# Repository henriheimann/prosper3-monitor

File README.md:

<br/>
<br/>
<br/>

# Prosper III Monitor

This repository contains the source code accompanying my master's thesis "Entwicklung einer digitalen Lösung zur Unterstützung von Tactical Urbanism auf Prosper III" (Development of a Digital Solution to Support Tactical Urbanism on Prosper III) at [Hochschule Ruhr West](https://www.hochschule-ruhr-west.de/). It includes hardware designs and embedded software for LoRaWAN-based sensor nodes to collect microclimate and irrigation data, as well as a web application and infrastructure to manage sensor nodes and view data.

<br/>
<br/>

Climate sensor nodes contain an ambient light sensor, a temperature and humidity sensor, as well as an optional infrared temperature sensor which can be used to measure surface temperatures from afar.

<br/>
<br/>
<br/>

Irrigation sensor nodes use a capacitive soil moisture sensor and the microcontrollers' embedded temperature sensor to monitor raised beds.

<br/>
<br/>

## Frontend

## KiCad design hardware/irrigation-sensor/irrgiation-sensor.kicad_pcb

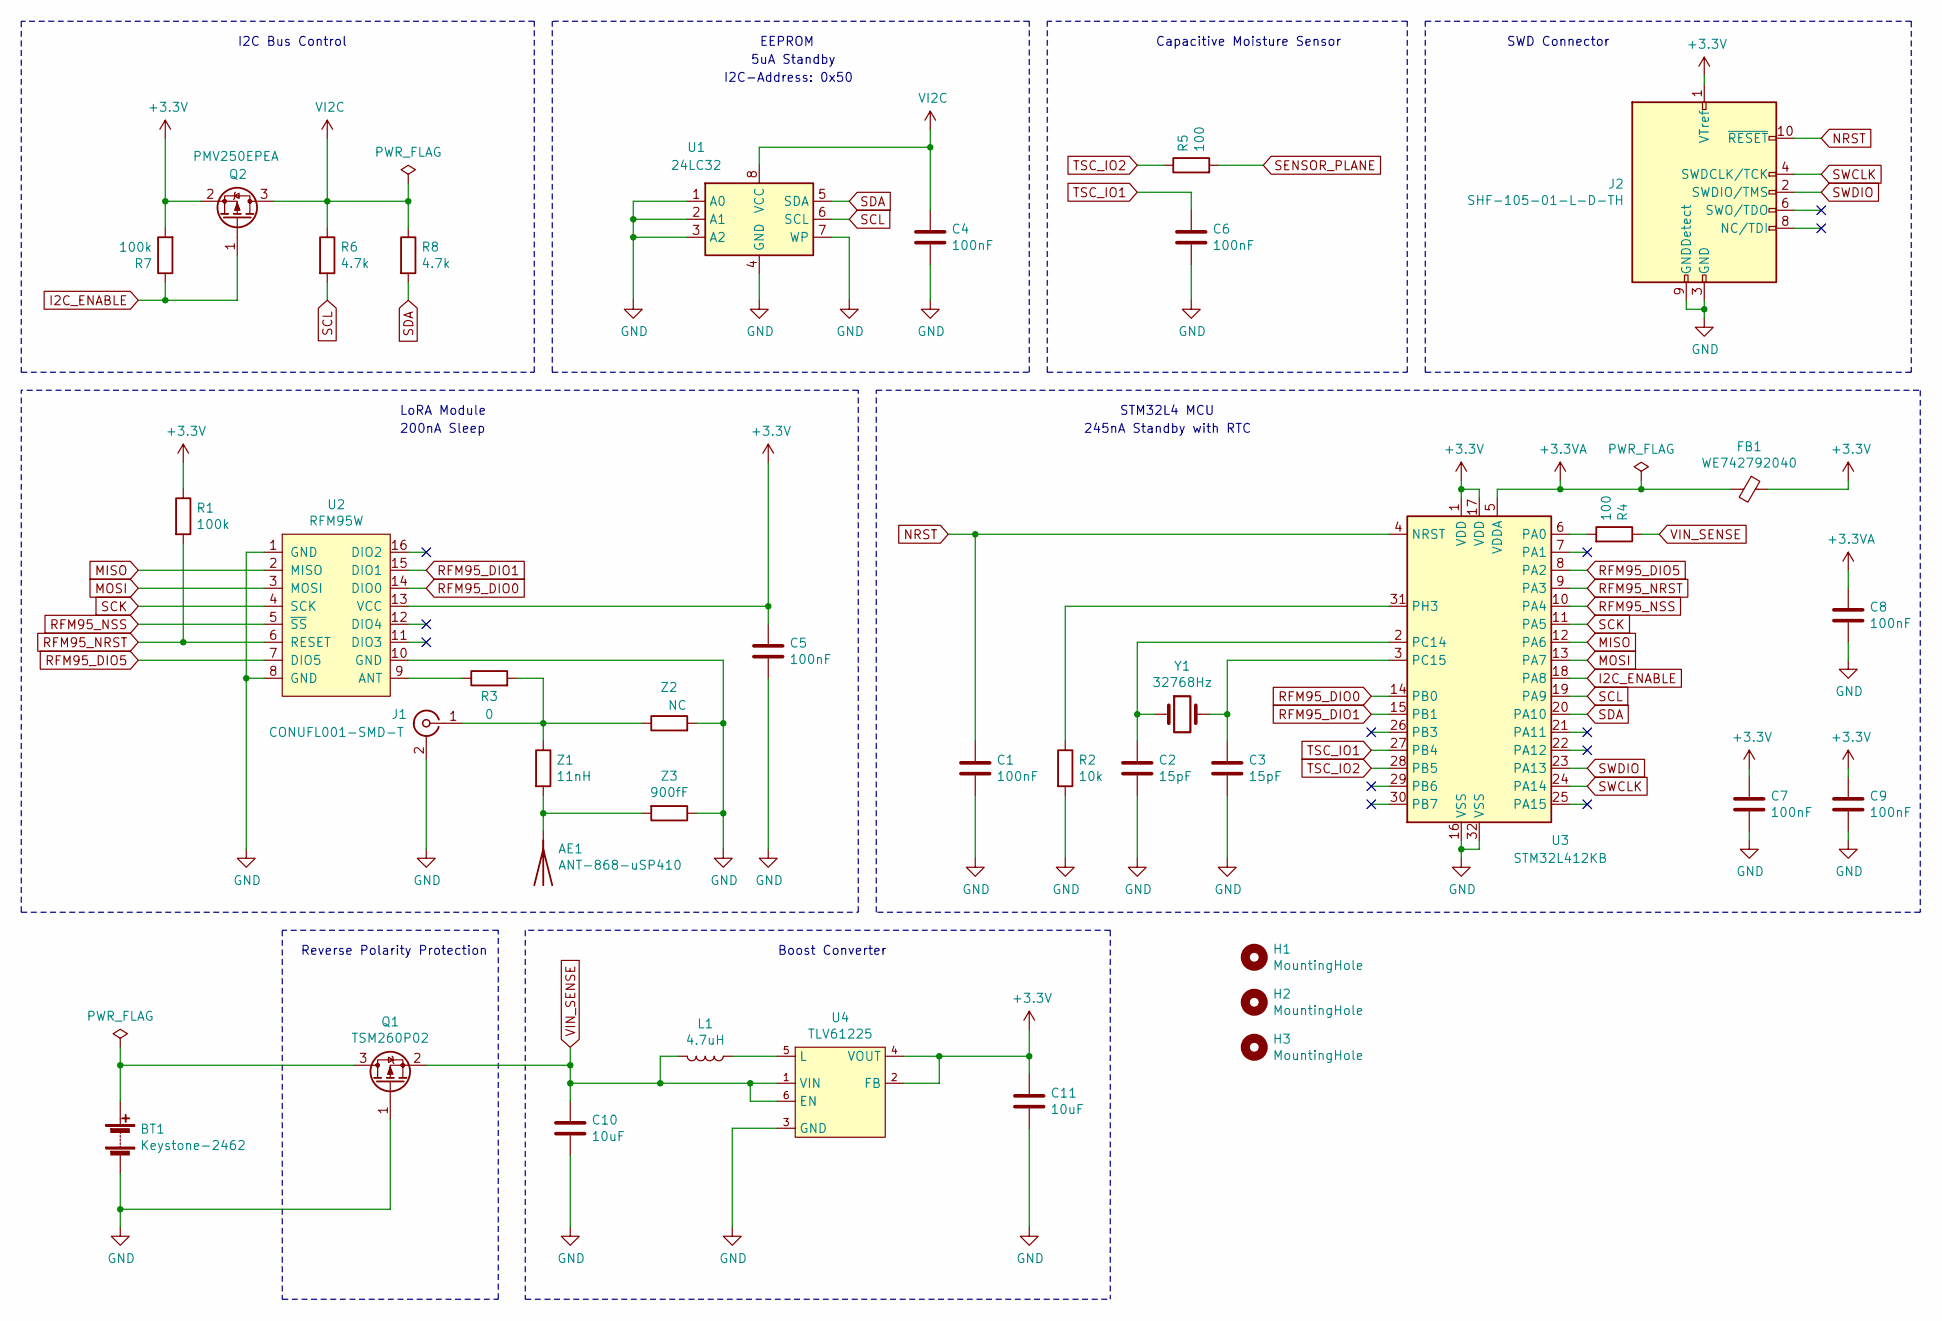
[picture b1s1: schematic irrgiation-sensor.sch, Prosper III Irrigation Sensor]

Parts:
AE1: ANT-868-uSP410; Linx_ANT-868-uSP410; mouser# 712-ANT-868-CHP-T; digikey# ANT-868-CHP-TCT-ND
BT1: Keystone-2462; BatteryHolder_Keystone_2468_2xAAA_NoSilkscreen; mouser# 534-2468; digikey# 36-2468-ND
C1, C4, C5, C6, C7, C8, C9: 100nF; C_0805_2012Metric_Pad1.18x1.45mm_HandSolder; mouser# 80-C0805C103K8R; digikey# C0805C103K8RAC7800
C2, C3: 15pF; C_0805_2012Metric_Pad1.18x1.45mm_HandSolder; mouser# 80-C0805C103K8R; digikey# C0805C103K8RAC7800
C10, C11: 10uF; C_0805_2012Metric_Pad1.18x1.45mm_HandSolder; mouser# 80-C0805C106K9P7210; digikey# 399-C0805C106K9PAC7210CT-ND
FB1: WE742792040; L_0805_2012Metric_Pad1.15x1.40mm_HandSolder; mouser# 710-742792040; digikey# 732-1620-1-ND
H1, H2, H3: MountingHole; MountingHole_2.2mm_M2
J1: CONUFL001-SMD-T; CONUFL001-SMD; mouser# 712-CONUFL001-SMD-T; digikey# CONUFL001-SMD-TCT-ND
J2: SHF-105-01-L-D-TH; SHF-105-01-L-D-TH_NoSilkscreen; mouser# 200-SHF10501LDTH; digikey# SAM11769-ND
L1: 4.7uH; L_Bourns-SRN4018_3DModel_HandSolder; mouser# 652-SRN4018TA-4R7M; digikey# SRN4018TA-4R7MTR-ND
Q1: TSM260P02; SOT-23
Q2: PMV250EPEA; SOT-23; mouser# 771-PMV250EPEAR; digikey# 1727-2303-1-ND
R1, R7: 100k; R_0805_2012Metric_Pad1.20x1.40mm_HandSolder; mouser# 603-RC0805FR-07100KL; digikey# 311-100KCRCT-ND
R2: 10k; R_0805_2012Metric_Pad1.20x1.40mm_HandSolder; mouser# 603-RC0805FR-0710KL; digikey# 311-10.0KCRCT-ND
R3: 0; R_0805_2012Metric_Pad1.20x1.40mm_HandSolder
R4: 100; R_0805_2012Metric_Pad1.20x1.40mm_HandSolder; mouser# 603-RC0805FR-07100RL; digikey# 311-100CRCT-ND
R5: 100; R_0805_2012Metric_Pad1.20x1.40mm_HandSolder; mouser# 603-RC0805FR-074K7L; digikey# 311-4.70KCRCT-ND
R6, R8: 4.7k; R_0805_2012Metric_Pad1.20x1.40mm_HandSolder; mouser# 603-RC0805FR-074K7L; digikey# 311-4.70KCRCT-ND
U1: 24LC32; SOIC-8_3.9x4.9mm_P1.27mm; mouser# 579-24LC32AT-I/SN; digikey# 24LC32AT-I/SNCT-ND
U2: RFM95W; mouser# 223-RFM95W-868S2; digikey# RFM95W-868S2-ND
U3: STM32L412KB; LQFP-32_7x7mm_P0.8mm_HandSolder; mouser# 511-STM32L412KBT6; digikey# 497-18229-ND
U4: TLV61225; SOT-363_SC-70-6_Handsoldering; mouser# 595-TLV61225DCKR; digikey# 296-36756-1-ND
Y1: 32768Hz; Crystal_SMD_EuroQuartz_EQ161-2Pin_3.2x1.5mm_HandSoldering
Z1: 11nH; R_0805_2012Metric_Pad1.20x1.40mm_HandSolder
Z2: NC; R_0805_2012Metric_Pad1.20x1.40mm_HandSolder
Z3: 900fF; R_0805_2012Metric_Pad1.20x1.40mm_HandSolder

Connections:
+3.3VA: C8.1, FB1.2, U3.5 (VDDA)
+3V3: C5.1, C7.1, C9.1, C11.1, FB1.1, J2.1 (VTref), Q2.2 (S), R1.1, R7.2, U2.13 (VCC), U3.1 (VDD), U3.17 (VDD), U4.2 (FB), U4.4 (VOUT)
GND: BT1.2 (-), C1.2, C2.2, C3.2, C4.2, C5.2, C6.2, C7.2, C8.2, C9.2, C10.2, C11.2, J1.2 (Ext), J2.3 (GND), J2.5 (GND), J2.9 (GNDDetect), Q1.1 (G), R2.2, U1.1 (A0), U1.2 (A1), U1.3 (A2), U1.4 (GND), U1.7 (WP), U2.1 (GND), U2.8 (GND), U2.10 (GND), U3.16 (VSS), U3.32 (VSS), U4.3 (GND), Z2.2, Z3.1
I2C_ENABLE: Q2.1 (G), R7.1, U3.18 (PA8)
MISO: U2.2 (MISO), U3.12 (PA6)
MOSI: U2.3 (MOSI), U3.13 (PA7)
NRST: C1.1, J2.10 (~RESET~), U3.4 (NRST)
unnamed: AE1.1, Z1.2, Z3.2
unnamed: BT1.1 (+), Q1.3 (D)
unnamed: C2.1, U3.2 (PC14), Y1.1
unnamed: C3.1, U3.3 (PC15), Y1.2
unnamed: J1.1 (In), R3.2, Z1.1, Z2.1
unnamed: L1.1, U4.5 (L)
unnamed: R2.1, U3.31 (PH3)
unnamed: R3.1, U2.9 (ANT)
unnamed: R4.2, U3.6 (PA0)
RFM95_DIO0: U2.14 (DIO0), U3.14 (PB0)
RFM95_DIO1: U2.15 (DIO1), U3.15 (PB1)
RFM95_DIO5: U2.7 (DIO5), U3.8 (PA2)
RFM95_NRST: R1.2, U2.6 (RESET), U3.9 (PA3)
RFM95_NSS: U2.5 (~SS), U3.10 (PA4)
SCK: U2.4 (SCK), U3.11 (PA5)
SCL: R6.2, U1.6 (SCL), U3.19 (PA9)
SDA: R8.2, U1.5 (SDA), U3.20 (PA10)
SENSOR_PLANE: R5.2
SWCLK: J2.4 (SWDCLK/TCK), U3.24 (PA14)
SWDIO: J2.2 (SWDIO/TMS), U3.23 (PA13)
TSC_IO1: C6.1, U3.27 (PB4)
TSC_IO2: R5.1, U3.28 (PB5)
VI2C: C4.1, Q2.3 (D), R6.1, R8.1, U1.8 (VCC)
VIN_SENSE: C10.1, L1.2, Q1.2 (S), R4.1, U4.1 (VIN), U4.6 (EN)

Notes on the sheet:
Reverse Polarity Protection
LoRA Module
I2C-Address: 0x50
EEPROM
5uA Standby
200nA Sleep
I2C Bus Control
Boost Converter
Capacitive Moisture Sensor
STM32L4 MCU
SWD Connector
245nA Standby with RTC

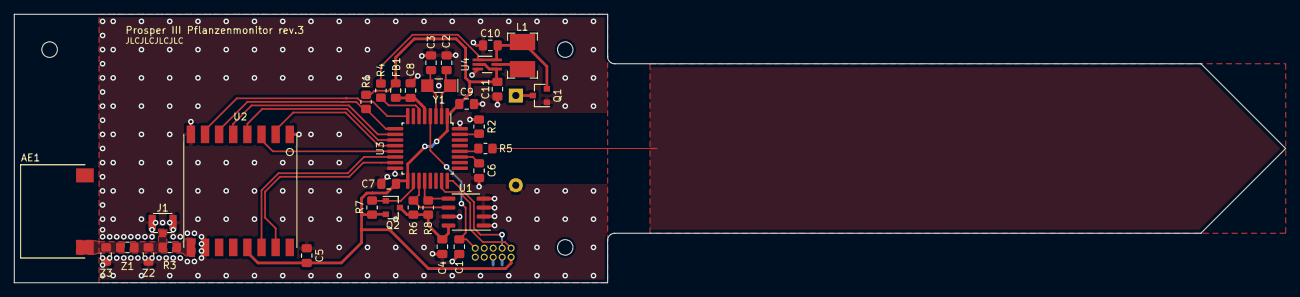
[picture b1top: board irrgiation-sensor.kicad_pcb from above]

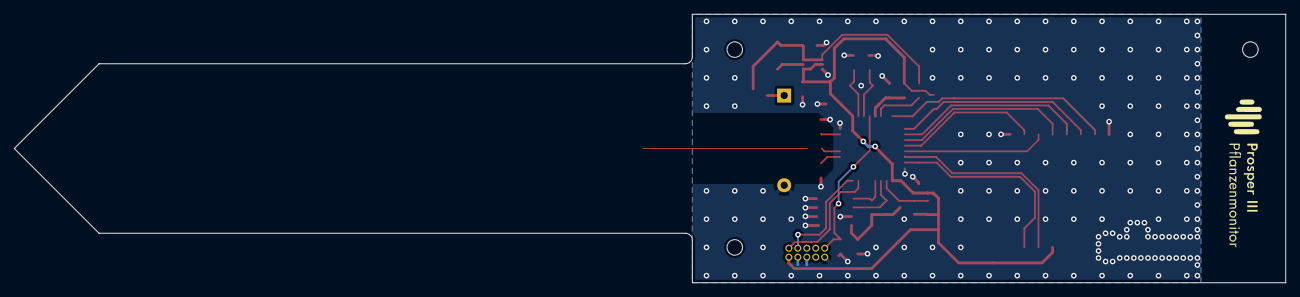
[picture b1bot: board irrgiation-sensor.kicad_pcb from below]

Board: 2 copper layers, 180.0 x 38.0 mm, 38 parts (2 on the bottom side), 30 nets.

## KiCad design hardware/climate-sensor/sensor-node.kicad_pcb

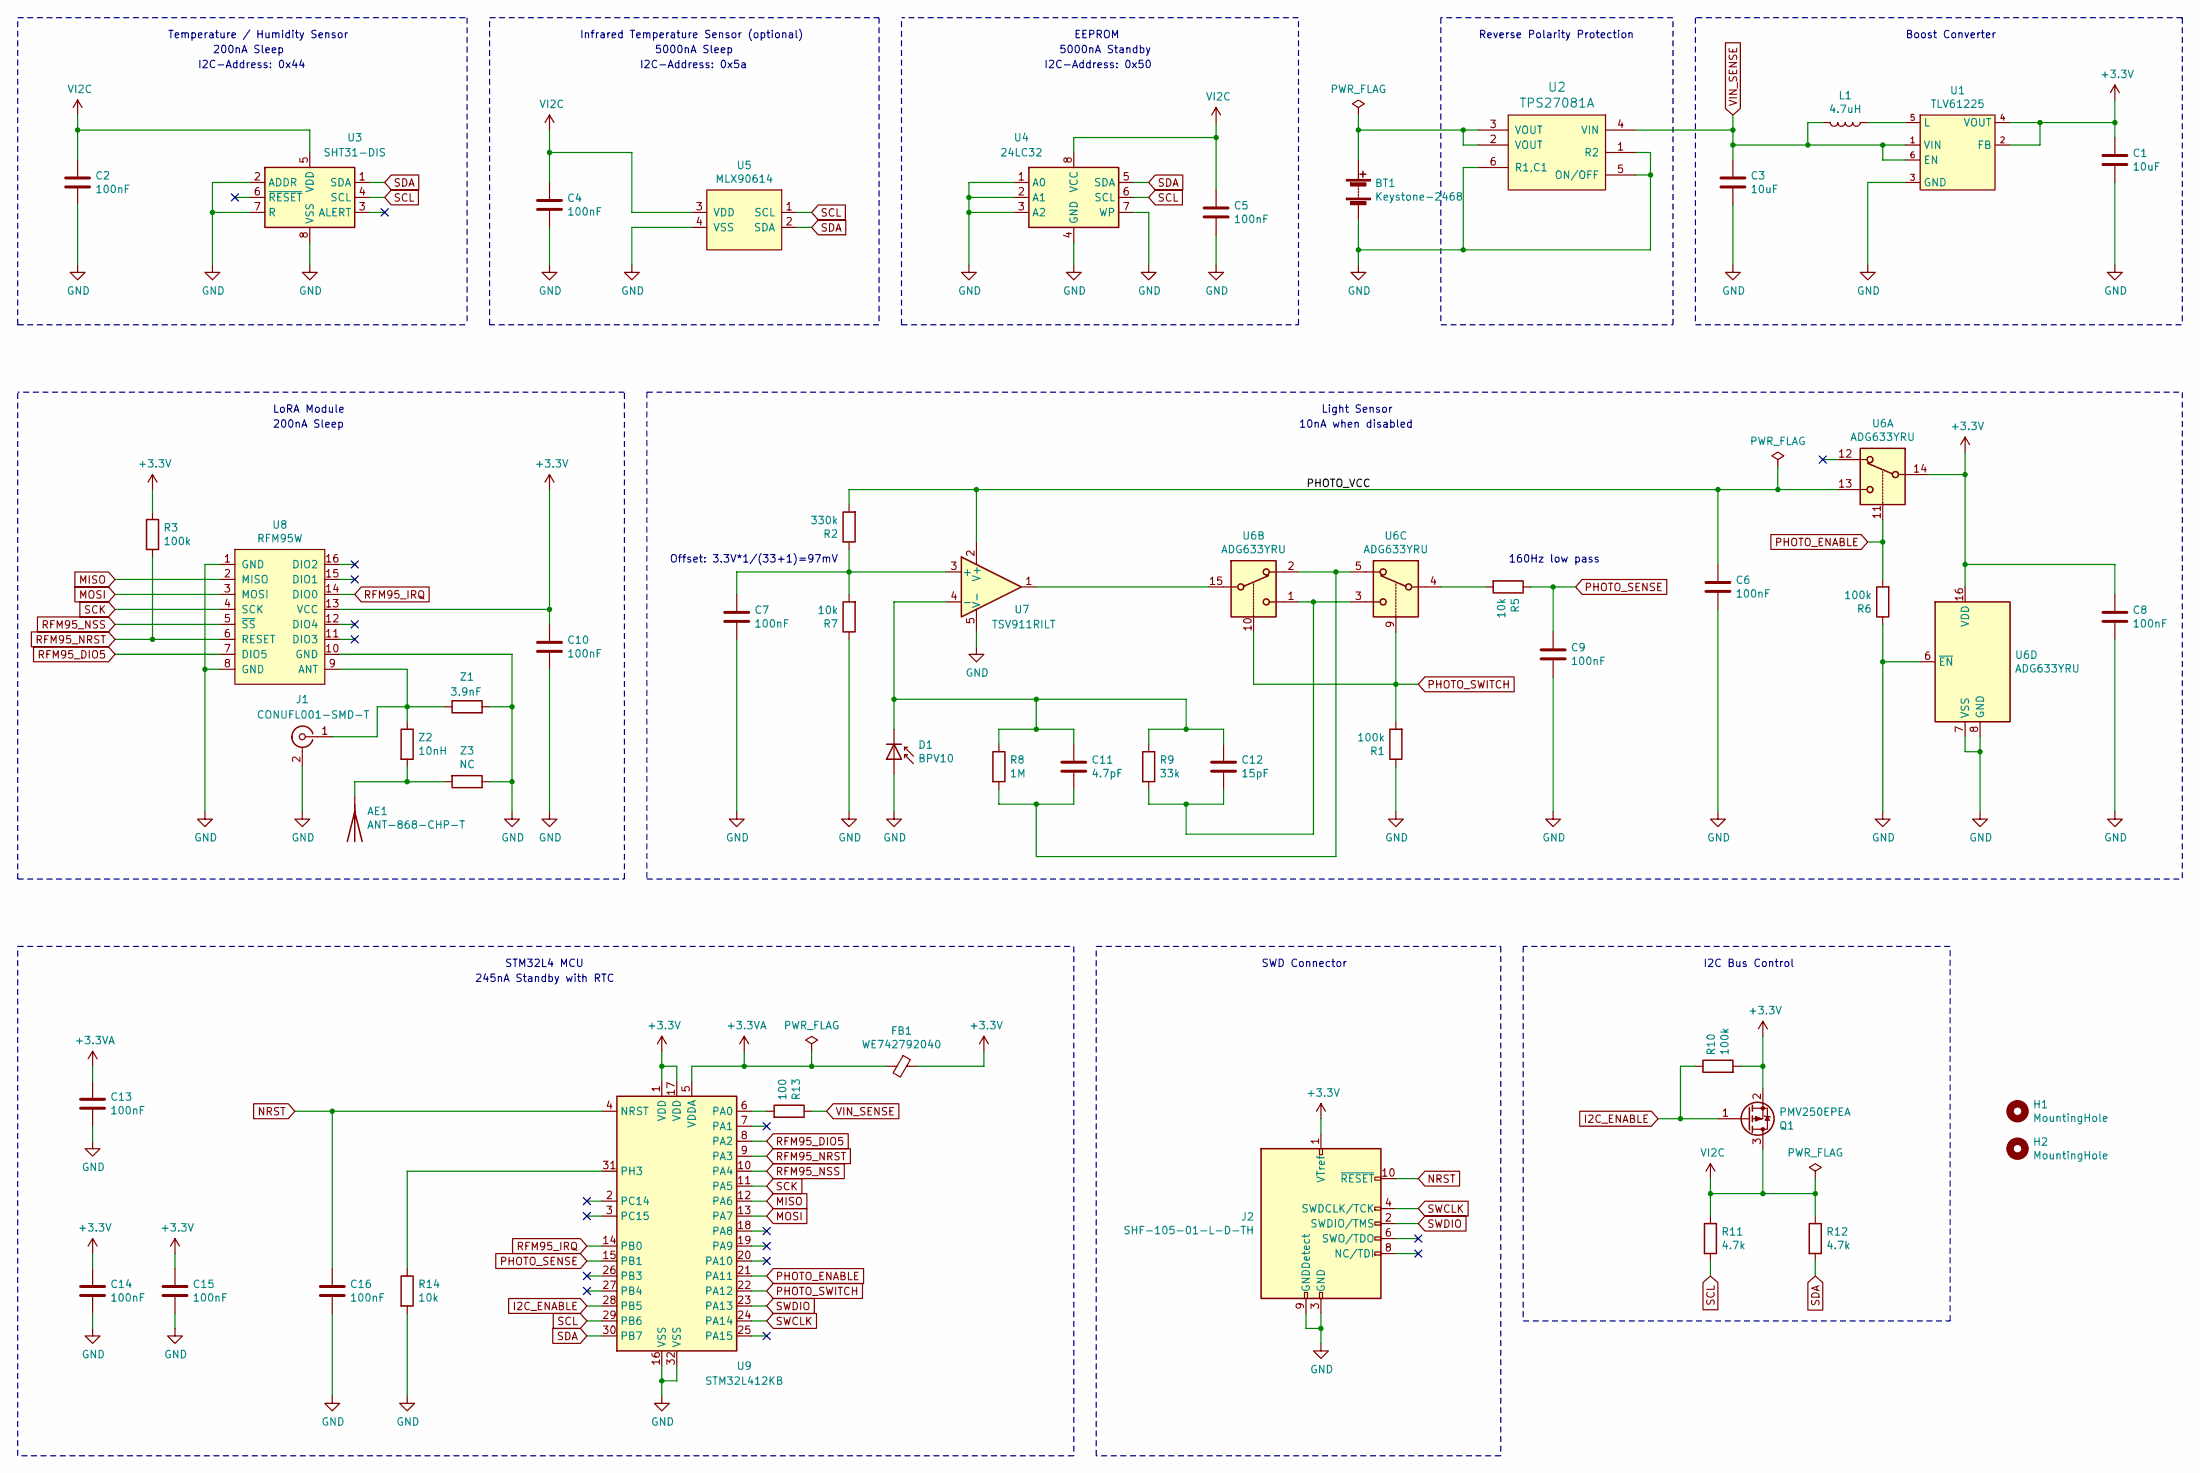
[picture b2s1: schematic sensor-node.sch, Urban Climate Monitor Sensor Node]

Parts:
AE1: ANT-868-CHP-T; Linx_ANT-868-CHP-T; mouser# 712-ANT-868-CHP-T; digikey# ANT-868-CHP-TCT-ND
BT1: Keystone-2468; BatteryHolder_Keystone_2468_2xAAA_NoSilkscreen; mouser# 534-2468; digikey# 36-2468-ND
C1, C3: 10uF; C_0805_2012Metric_Pad1.18x1.45mm_HandSolder; mouser# 80-C0805C106K9P7210; digikey# 399-C0805C106K9PAC7210CT-ND
C2, C4, C5, C6, C7, C8, C9, C10, C13, C14, C15, C16: 100nF; C_0805_2012Metric_Pad1.18x1.45mm_HandSolder; mouser# 80-C0805C103K8R; digikey# C0805C103K8RAC7800
C11: 4.7pF; C_0805_2012Metric_Pad1.18x1.45mm_HandSolder; mouser# 80-C0805C479C8HACTU; digikey# C0805C479C8HAC7800-ND
C12: 15pF; C_0805_2012Metric_Pad1.18x1.45mm_HandSolder; mouser# 80-C0805C150M8HACTU; digikey# C0805C150M8HAC7800
D1: BPV10; LED_D5.0mm_Clear; mouser# 782-BPV10; digikey# 751-1001-ND
FB1: WE742792040; L_0805_2012Metric_Pad1.15x1.40mm_HandSolder; mouser# 710-742792040; digikey# 732-1620-1-ND
H1, H2: MountingHole; MountingHole_2.2mm_M2
J1: CONUFL001-SMD-T; CONUFL001-SMD; mouser# 712-CONUFL001-SMD-T; digikey# CONUFL001-SMD-TCT-ND
J2: SHF-105-01-L-D-TH; mouser# 200-SHF10501LDTH; digikey# SAM11769-ND
L1: 4.7uH; L_Bourns-SRN4018_With3DModel; mouser# 652-SRN4018TA-4R7M; digikey# SRN4018TA-4R7MTR-ND
Q1: PMV250EPEA; SOT-23; mouser# 771-PMV250EPEAR; digikey# 1727-2303-1-ND
R1, R6: 100k; R_0805_2012Metric_Pad1.20x1.40mm_HandSolder; mouser# 603-RC0805FR-0710KL; digikey# 311-10.0KCRCT-ND
R2: 330k; R_0805_2012Metric_Pad1.20x1.40mm_HandSolder; mouser# 603-RC0805FR-07330KL; digikey# 311-330KCRCT-ND
R3, R10: 100k; R_0805_2012Metric_Pad1.20x1.40mm_HandSolder; mouser# 603-RC0805FR-07100KL; digikey# 311-100KCRCT-ND
R5, R7, R14: 10k; R_0805_2012Metric_Pad1.20x1.40mm_HandSolder; mouser# 603-RC0805FR-0710KL; digikey# 311-10.0KCRCT-ND
R8: 1M; R_0805_2012Metric_Pad1.20x1.40mm_HandSolder; mouser# 603-RC0805FR-071ML; digikey# 311-1.00MCRCT-ND
R9: 33k; R_0805_2012Metric_Pad1.20x1.40mm_HandSolder; mouser# 603-RC0805FR-0733KL; digikey# 311-33.0KCRCT-ND
R11, R12: 4.7k; R_0805_2012Metric_Pad1.20x1.40mm_HandSolder; mouser# 603-RC0805FR-074K7L; digikey# 311-4.70KCRCT-ND
R13: 100; R_0805_2012Metric_Pad1.15x1.40mm_HandSolder; mouser# 603-RC0805FR-07100RL; digikey# 311-100CRCT-ND
U1: TLV61225; SC-70-6; mouser# 595-TLV61225DCKR; digikey# 296-36756-1-ND
U2: TPS27081A; TSOT-23-6; mouser# 595-TPS27081ADDCR; digikey# 296-34970-1-ND
U3: SHT31-DIS; Sensirion_DFN-8-1EP_2.5x2.5mm_P0.5mm_EP1.1x1.7mm; mouser# 403-SHT31-DIS-F; digikey# 1649-1066-1-ND
U4: 24LC32; SOIC-8_3.9x4.9mm_P1.27mm; mouser# 579-24LC32AT-I/SN; digikey# 24LC32AT-I/SNCT-ND
U5: MLX90614; TO-39-4; mouser# 482-90614ESFBCC000TU; digikey# MLX90614ESF-BCC-000-TU-ND
U6: ADG633YRU; TSSOP-16_4.4x5mm_P0.65mm; mouser# 584-ADG633YRUZ; digikey# ADG633YRUZ-ND
U7: TSV911RILT; SOT-23-5; mouser# 511-TSV911RILT; digikey# 497-10538-1-ND
U8: RFM95W; mouser# 223-RFM95W-868S2; digikey# RFM95W-868S2-ND
U9: STM32L412KB; LQFP-32_7x7mm_P0.8mm; mouser# 511-STM32L412KBT6; digikey# 497-18229-ND
Z1: 3.9nF; R_0805_2012Metric_Pad1.20x1.40mm_HandSolder
Z2: 10nH; R_0805_2012Metric_Pad1.20x1.40mm_HandSolder
Z3: NC; R_0805_2012Metric_Pad1.20x1.40mm_HandSolder

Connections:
+3.3VA: C13.1, FB1.2, U9.5 (VDDA)
+3V3: C1.1, C8.1, C10.1, C14.1, C15.1, FB1.1, J2.1 (VTref), Q1.2 (S), R3.1, R10.2, U1.2 (FB), U1.4 (VOUT), U6.14, U6.16 (VDD), U8.13 (VCC), U9.1 (VDD), U9.17 (VDD)
/PHOTO_VCC: C6.1, R2.2, U6.13, U7.2 (V+)
GND: BT1.2 (-), C1.2, C2.2, C3.2, C4.2, C5.2, C6.2, C7.2, C8.2, C9.2, C10.2, C13.2, C14.2, C15.2, C16.2, D1.2 (A), J1.2 (Ext), J2.3 (GND), J2.5 (GND), J2.9 (GNDDetect), R1.1, R6.1, R7.1, R14.2, U1.3 (GND), U2.1 (R2), U2.5 (ON/OFF), U2.6 (R1,C1), U3.2 (ADDR), U3.7 (R), U3.8 (VSS), U3.9 (VSS), U4.1 (A0), U4.2 (A1), U4.3 (A2), U4.4 (GND), U4.7 (WP), U5.4 (VSS), U6.6 (~EN), U6.7 (VSS), U6.8 (GND), U7.5 (V-), U8.1 (GND), U8.8 (GND), U8.10 (GND), U9.16 (VSS), U9.32 (VSS), Z1.2, Z3.1
I2C_ENABLE: Q1.1 (G), R10.1, U9.28 (PB5)
MISO: U8.2 (MISO), U9.12 (PA6)
MOSI: U8.3 (MOSI), U9.13 (PA7)
NRST: C16.1, J2.10 (~RESET~), U9.4 (NRST)
unnamed: AE1.1, Z2.2, Z3.2
unnamed: BT1.1 (+), U2.2 (VOUT), U2.3 (VOUT)
unnamed: C7.1, R2.1, R7.2, U7.3 (+)
unnamed: C11.1, C12.1, D1.1 (K), R8.1, R9.1, U7.4 (-)
unnamed: C11.2, R8.2, U6.2, U6.5
unnamed: C12.2, R9.2, U6.1, U6.3
unnamed: J1.1 (In), U8.9 (ANT), Z1.1, Z2.1
unnamed: L1.1, U1.5 (L)
unnamed: R5.2, U6.4
unnamed: R13.2, U9.6 (PA0)
unnamed: R14.1, U9.31 (PH3)
unnamed: U6.15, U7.1
PHOTO_ENABLE: R6.2, U6.11, U9.21 (PA11)
PHOTO_SENSE: C9.1, R5.1, U9.15 (PB1)
PHOTO_SWITCH: R1.2, U6.9, U6.10, U9.22 (PA12)
RFM95_DIO5: U8.7 (DIO5), U9.8 (PA2)
RFM95_IRQ: U8.14 (DIO0), U9.14 (PB0)
RFM95_NRST: R3.2, U8.6 (RESET), U9.9 (PA3)
RFM95_NSS: U8.5 (~SS), U9.10 (PA4)
SCK: U8.4 (SCK), U9.11 (PA5)
SCL: R11.2, U3.4 (SCL), U4.6 (SCL), U5.1 (SCL), U9.29 (PB6)
SDA: R12.2, U3.1 (SDA), U4.5 (SDA), U5.2 (SDA), U9.30 (PB7)
SWCLK: J2.4 (SWDCLK/TCK), U9.24 (PA14)
SWDIO: J2.2 (SWDIO/TMS), U9.23 (PA13)
VI2C: C2.1, C4.1, C5.1, Q1.3 (D), R11.1, R12.1, U3.5 (VDD), U4.8 (VCC), U5.3 (VDD)
VIN_SENSE: C3.1, L1.2, R13.1, U1.1 (VIN), U1.6 (EN), U2.4 (VIN)

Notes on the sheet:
Reverse Polarity Protection
Boost Converter
SWD Connector
STM32L4 MCU
I2C-Address: 0x44
I2C-Address: 0x5a
Offset: 3.3V*1/(33+1)=97mV
Infrared Temperature Sensor (optional)
Temperature / Humidity Sensor
LoRA Module
Light Sensor
I2C-Address: 0x50
EEPROM
5000nA Sleep
200nA Sleep
5000nA Standby
245nA Standby with RTC
10nA when disabled
160Hz low pass
I2C Bus Control

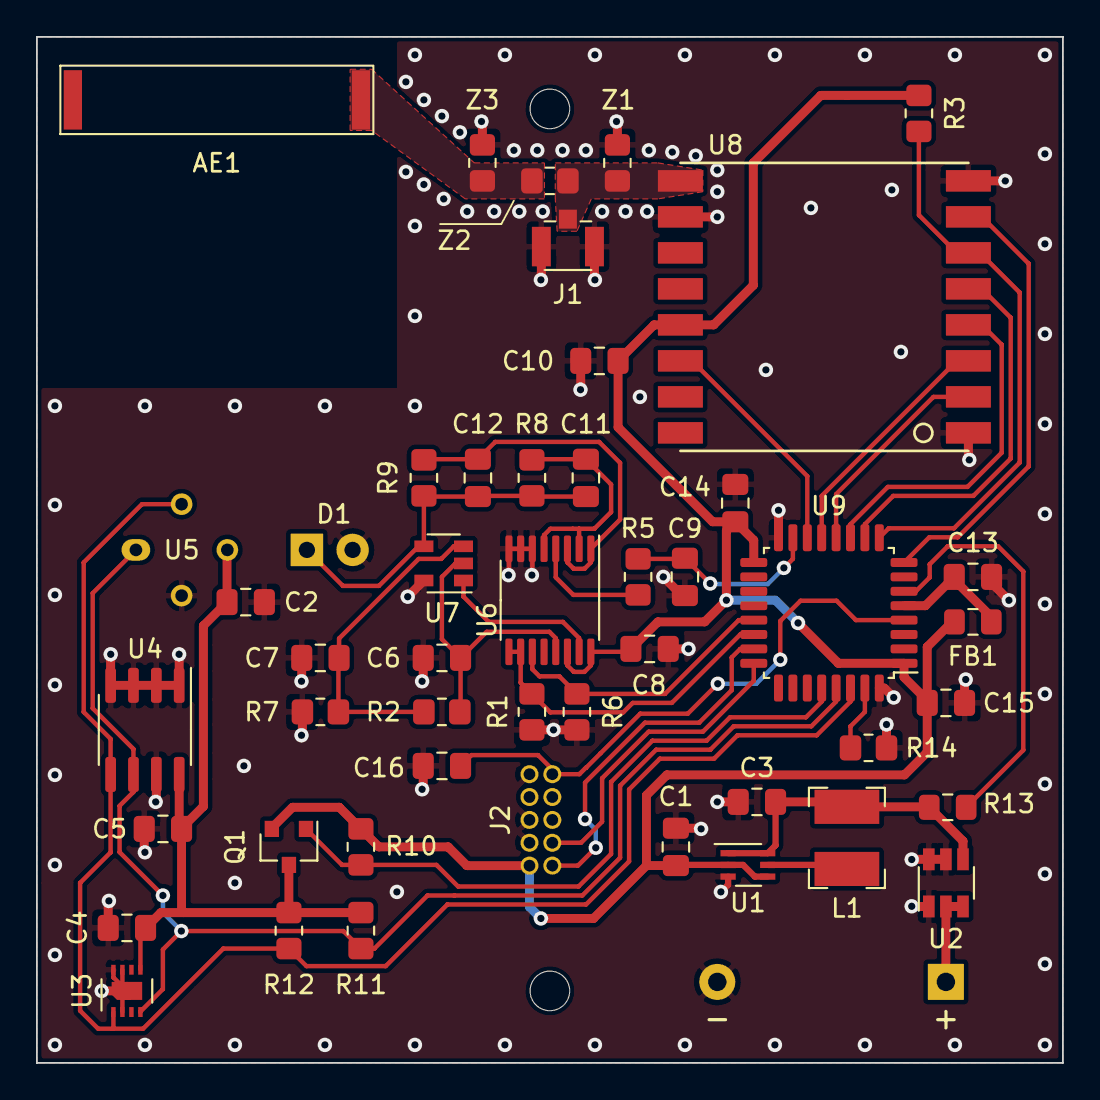
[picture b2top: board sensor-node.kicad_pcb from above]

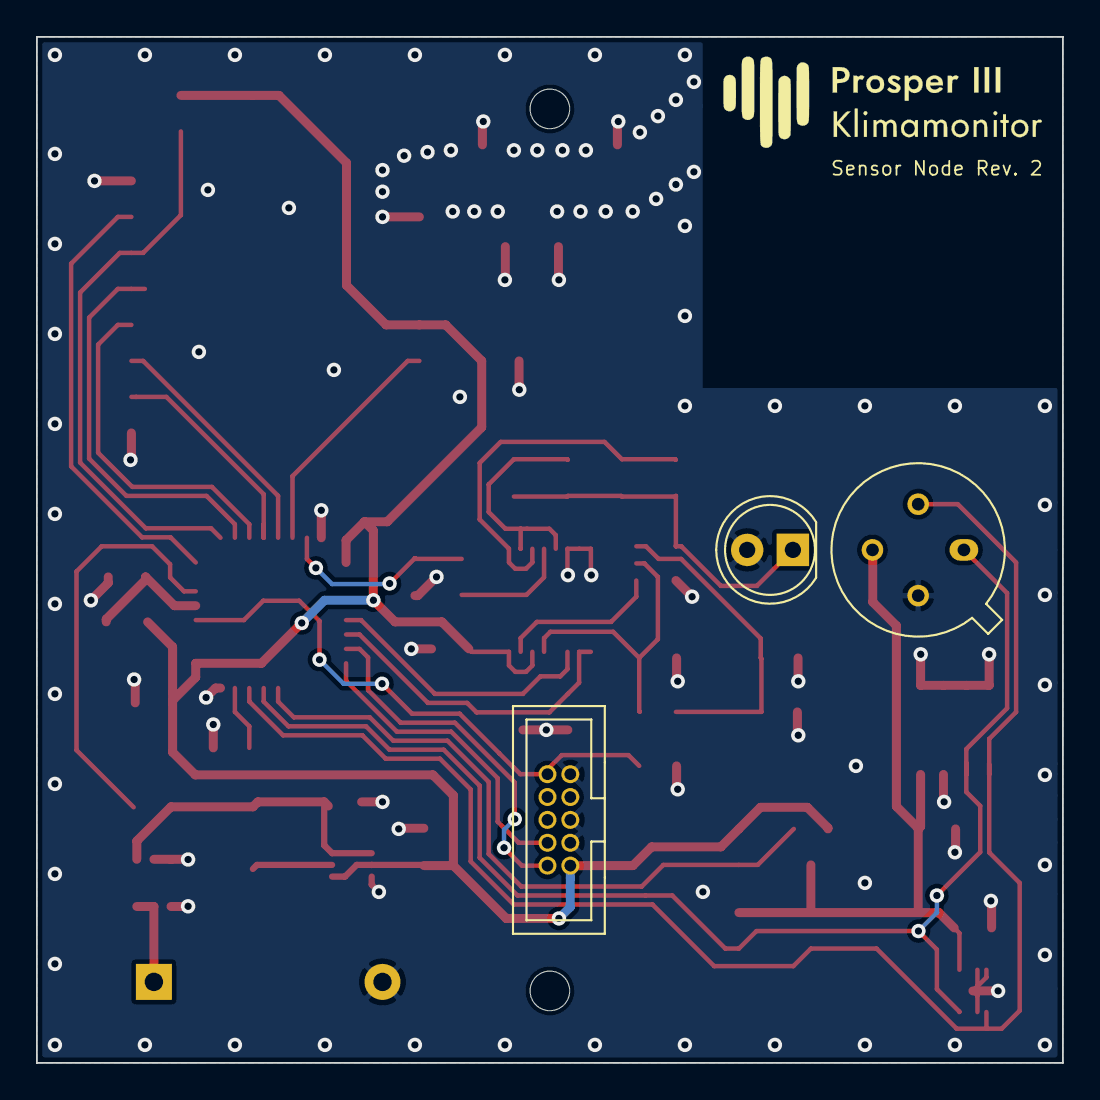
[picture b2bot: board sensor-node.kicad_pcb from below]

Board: 2 copper layers, 57.0 x 57.0 mm, 51 parts (4 on the bottom side), 34 nets.

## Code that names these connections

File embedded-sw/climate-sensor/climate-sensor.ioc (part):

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Mcu.Name=STM32L412KBUx
Mcu.Package=UFQFPN32
Mcu.UserName=STM32L412KBUx
PA0-CK_IN.GPIOParameters=GPIO_Label
PA0-CK_IN.GPIO_Label=VIN_SENSE
PA0-CK_IN.Signal=ADCx_IN5
PA11.GPIOParameters=GPIO_Label
PA11.GPIO_Label=PHOTO_ENABLE
PA11.Signal=GPIO_Output
PA12.GPIOParameters=GPIO_PuPd,GPIO_Label
PA12.GPIO_Label=PHOTO_SWITCH
PA12.GPIO_PuPd=GPIO_PULLDOWN
PA12.Signal=GPIO_Output
PA13\ (JTMS/SWDIO).GPIOParameters=GPIO_Label
PA13\ (JTMS/SWDIO).GPIO_Label=SWDIO
PA13\ (JTMS/SWDIO).Mode=Serial_Wire
PA13\ (JTMS/SWDIO).Signal=SYS_JTMS-SWDIO
PA14\ (JTCK/SWCLK).GPIOParameters=GPIO_Label
PA14\ (JTCK/SWCLK).GPIO_Label=SWCLK
PA14\ (JTCK/SWCLK).Mode=Serial_Wire
PA14\ (JTCK/SWCLK).Signal=SYS_JTCK-SWCLK
PA2.GPIOParameters=GPIO_Label
PA2.GPIO_Label=RFM95_DIO5
PA2.Signal=GPXTI2
PA3.GPIOParameters=GPIO_Label
PA3.GPIO_Label=RFM95_NRST
PA3.Signal=GPIO_Output
PA4.GPIOParameters=PinState,GPIO_Label
PA4.GPIO_Label=RFM95_NSS
PA4.PinState=GPIO_PIN_SET
PA4.Signal=GPIO_Output
PA5.Mode=Full_Duplex_Master
PA5.Signal=SPI1_SCK
PA6.Mode=Full_Duplex_Master
PA6.Signal=SPI1_MISO
PA7.Mode=Full_Duplex_Master
PA7.Signal=SPI1_MOSI
PB0.GPIOParameters=GPIO_Label
PB0.GPIO_Label=RFM95_DIO0
PB0.Signal=GPXTI0
PB1.GPIOParameters=GPIO_Label
PB1.GPIO_Label=PHOTO_SENSE
PB1.Signal=ADCx_IN16
PB5.GPIOParameters=PinState,GPIO_Label
PB5.GPIO_Label=I2C_ENABLE
PB5.PinState=GPIO_PIN_SET
PB5.Signal=GPIO_Output
PB6.GPIOParameters=GPIO_Pu
PB6.GPIO_Pu=GPIO_NOPULL
PB6.Mode=I2C
PB6.Signal=I2C1_SCL
PB7.GPIOParameters=GPIO_Pu
PB7.GPIO_Pu=GPIO_NOPULL
PB7.Mode=I2C
PB7.Signal=I2C1_SDA
RCC.HSE_VALUE=8000000
RCC.SYSCLKFreq_VALUE=32000000
board=NUCLEO-L412KB
boardIOC=true

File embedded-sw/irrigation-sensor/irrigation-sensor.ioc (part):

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Mcu.Name=STM32L422KBTx
Mcu.Package=LQFP32
Mcu.UserName=STM32L422KBTx
PA0-CK_IN.GPIOParameters=GPIO_Label
PA0-CK_IN.GPIO_Label=VIN_SENSE
PA0-CK_IN.Signal=ADCx_IN5
PA10.Mode=I2C
PA10.Signal=I2C1_SDA
PA13\ (JTMS/SWDIO).Mode=Serial_Wire
PA13\ (JTMS/SWDIO).Signal=SYS_JTMS-SWDIO
PA14\ (JTCK/SWCLK).Mode=Serial_Wire
PA14\ (JTCK/SWCLK).Signal=SYS_JTCK-SWCLK
PA2.GPIOParameters=GPIO_PuPd,GPIO_Label
PA2.GPIO_Label=RFM95_DIO5
PA2.GPIO_PuPd=GPIO_NOPULL
PA2.Signal=GPXTI2
PA3.GPIOParameters=GPIO_Label
PA3.GPIO_Label=RFM95_NRST
PA3.Signal=GPIO_Output
PA4.GPIOParameters=PinState,GPIO_Label
PA4.GPIO_Label=RFM95_NSS
PA4.PinState=GPIO_PIN_SET
PA4.Signal=GPIO_Output
PA5.Mode=Full_Duplex_Master
PA5.Signal=SPI1_SCK
PA6.Mode=Full_Duplex_Master
PA6.Signal=SPI1_MISO
PA7.Mode=Full_Duplex_Master
PA7.Signal=SPI1_MOSI
PA8.GPIOParameters=PinState,GPIO_PuPd,GPIO_Label
PA8.GPIO_Label=I2C_ENABLE
PA8.GPIO_PuPd=GPIO_NOPULL
PA8.PinState=GPIO_PIN_SET
PA8.Signal=GPIO_Output
PA9.Mode=I2C
PA9.Signal=I2C1_SCL
PB0.GPIOParameters=GPIO_PuPd,GPIO_Label
PB0.GPIO_Label=RFM95_DIO0
PB0.GPIO_PuPd=GPIO_NOPULL
PB0.Signal=GPXTI0
PB1.GPIOParameters=GPIO_PuPd,GPIO_Label
PB1.GPIO_Label=RFM95_DIO1
PB1.GPIO_PuPd=GPIO_NOPULL
PB1.Signal=GPXTI1
PB4\ (NJTRST).Mode=G2_IO1-Sampling
PB4\ (NJTRST).Signal=TSC_G2_IO1
PB5.Mode=G2_IO2-Channel
PB5.Signal=TSC_G2_IO2
PC14-OSC32_IN\ (PC14).Mode=LSE-External-Oscillator
PC14-OSC32_IN\ (PC14).Signal=RCC_OSC32_IN
PC15-OSC32_OUT\ (PC15).Mode=LSE-External-Oscillator
PC15-OSC32_OUT\ (PC15).Signal=RCC_OSC32_OUT
RCC.HSE_VALUE=8000000
RCC.SYSCLKFreq_VALUE=32000000
board=custom

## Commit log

2021-12-11 Add sensor nodes hardware files and irrigation sensor embedded project
2021-12-11 Add frontend, embedded submodules, local dev environment
2021-12-16 Add embedded projects, basic backend setup
2021-12-29 Start backend TTN integration, irrigation sensor embedded software implementation
2021-12-30 Setup local-production deployment
2022-01-02 PCB revision 2, add data packet handling to climate-sensor
2022-01-02 Add 3d model and plot for irrigation sensor node
2022-01-21 Implement user management and authorization
2022-01-22 Update Pflanzenmonitor logo, start IntegrationTest implementation
2022-01-22 Implement more tests and add github workflow
2022-01-22 Finish UserControllerIntegrationTest
2022-01-22 Add TokenServiceTest
2022-01-22 Add AuthServiceTest and AuthControllerIntegrationTest
2022-01-22 Fix LoginRequest construction
2022-01-29 Implement downlink functionality
2022-01-30 Renaming of uem to p3m(onitor)
2022-02-06 Finish implementation of administration
2022-02-07 Add prettier to frontend and format
2022-02-10 Add maps in frontend
2022-02-10 Add sensor details popup
2022-02-18 Implement display of sensor measurements in frontend
2022-02-22 Refactor backend packet structure, start frontend widget implementation
2022-02-27 Add watchdog and disable adaptive data rate during device creation
2022-02-28 Add design files and add finish frontend plant widget
2022-03-03 Fix map size after load, add sensor dashboard page
2022-03-06 Update climate sensors embedded software
2022-03-06 Fix grafana button and update telegaf configurations for OpenWeaterMap
2022-03-10 Add mapping to qr codes and update embedded software submodules
2022-03-17 Add different irrigation sensor hardware revisions and cypress e2e tests
2022-03-17 Use correct username in InfluxDbService, fix e2e pipeline directory
2022-03-17 Set deployment script interpreter from zsh to bash
2022-03-17 Set docker pipeline build and target platforms
2022-03-17 Add .gitattributes for generate code
2022-03-18 Try fixing e2e docker env build variables
2022-03-18 Add backend unit tests for devices and mqtt, influxdb, telegraf integration testing
2022-03-19 Add deployment to workflows
2022-04-12 Update sensor QR scan dashboard
2022-04-12 Fix sensor dashboard page
2022-04-12 Fix router links
2022-04-12 Try to fix build script
2022-04-22 Add TTN sync e2e test
2022-04-22 Add grafana and api doc as iframe, add configuration for moistre counter and brightness
2022-04-22 Update backend tests
2022-04-22 Upload cypress screenshots and videos
2022-04-22 Prolongue wait time before running e2e tests
2022-04-22 Add loading spinners to main dashboard
2022-04-22 Update locale, fix measurement visualisation
